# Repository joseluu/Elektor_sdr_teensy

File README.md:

### SDR front end for teensy and teensy audio

This frontend board stacks on top of a teensyaudio board which iself is stacked on the teensy.

<p align="center">
  <table style="width:100%">
    <tr>
      <td></td>
      <td></td>
      <td></td>
      <td></td>
    </tr>
  </table>
</p>

Teensy 4.0 is used, schematic is heavily inspired by the Elektor board: https://www.elektormagazine.fr/labs/software-defined-radio-sdr-shield-for-arduino-150515-1

The differences are:

The frequency is not divided by 4 to make quadrature signals (no 7474 flipflops), rather the quadrature will have to be generated by the si5351.
A provision for an external oscillator input is made (V1.0 only), it uses a separate SMA

PCB layout attempts to minimize noise with separate ground planes for digital and analog

Versions (V2.0 is in its own branch):

<p align="center">
</td>
</p>

V 1.1 fixes a cabling error to two of the 6022 op-amps, removes the external oscillator input, internally connects the 3rd output of the si5351 frequency synthetiser to the input allowing fot tests and calibration of the signal path

V 1.1 uses a 74HC4066 multiplexer and is good to 30MHz, has a cabling error underneath where the zero ohm resistor connecting the 2 ground plane is not connected on one side.

V 2.0 uses a SN74CBTL3253 and should be good to 150MHz (work in progress, not tested yet)

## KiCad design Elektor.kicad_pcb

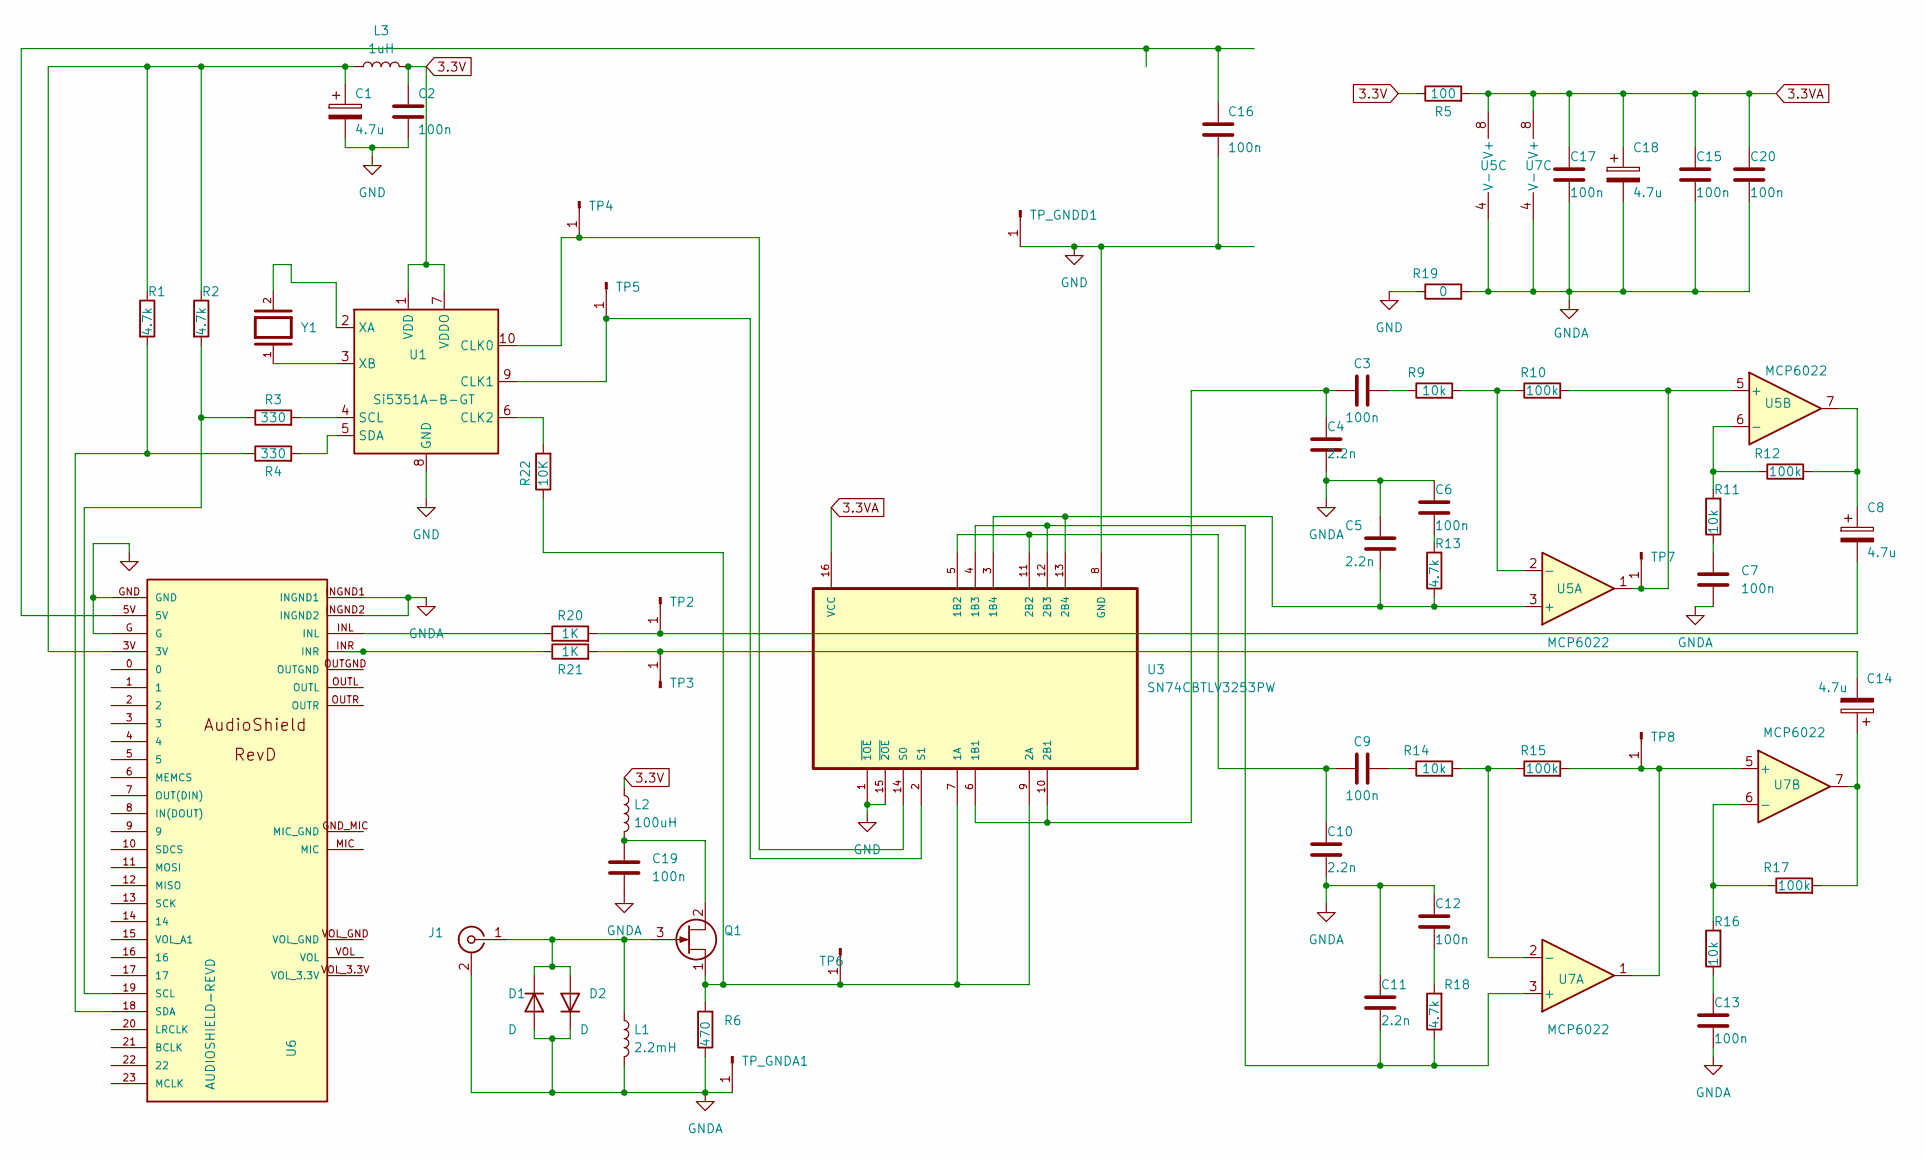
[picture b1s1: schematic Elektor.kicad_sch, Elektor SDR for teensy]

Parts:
C1, C8, C14, C18: 4.7u; C_Rect_L4.0mm_W2.5mm_P2.50mm
C2, C3, C6, C7, C9, C12, C13, C15, C16, C17, C19, C20: 100n; C_0603_1608Metric
C4, C5, C10, C11: 2.2n; C_0603_1608Metric
D1, D2: D; D_SOD-123
J1: Conn_Coaxial; SMA_Samtec_SMA-J-P-X-ST-EM1_EdgeMount
L1: 2.2mH; L_1812_4532Metric
L2: 100uH; L_1210_3225Metric
L3: 1uH; L_0805_2012Metric_Pad1.05x1.20mm_HandSolder
Q1: BF545B; SOT-23
R1, R2, R13, R18: 4.7k; R_0603_1608Metric
R3, R4: 330; R_0603_1608Metric
R5: 100; R_0603_1608Metric
R6: 470; R_0603_1608Metric
R9, R11, R14, R16: 10k; R_0603_1608Metric
R10, R12, R15, R17: 100k; R_0603_1608Metric
R19: 0; R_0603_1608Metric
R20, R21: 1K; R_0603_1608Metric
R22: 10K; R_0402_1005Metric
TP2, TP3, TP4, TP5, TP6, TP7, TP8: Conn_01x01_Pin; Test_point_jose_D1.8mm_Drill1.0mm
TP_GNDA1: Conn_01x01_Pin; Test_point_jose_D1.8mm_Drill1.0mm
TP_GNDD1: Conn_01x01_Pin; Test_point_jose_D1.8mm_Drill1.0mm
U1: Si5351A-B-GT; MSOP-10_3x3mm_P0.5mm
U3: SN74CBTLV3253PW; TSSOP-16_4.4x5mm_P0.65mm
U5, U7: MCP6022; SOP-8_3.9x4.9mm_P1.27mm
U6: AUDIOSHIELD-REVD; AUDIOSHIELD-REVD-Simplified
Y1: ABM7-25.000MHZ-D2Y-T; XTAL_ABM7-16.000MHZ-D2Y-T; PARTREV 9/3/2019

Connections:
3.3V: C2.1, L2.1, L3.2, R5.1, U1.1 (VDD), U1.7 (VDDO)
3.3VA: C15.1, C17.1, C18.1, C20.1, R5.2, U3.16 (VCC), U5.8 (V+), U7.8 (V+)
GND: C1.2, C2.2, C16.2, R19.1, TP_GNDD1.1, U1.8 (GND), U3.1 (~1OE), U3.8 (GND), U3.15 (~2OE), U6.G, U6.GND
GNDA: C4.1, C5.2, C6.1, C7.1, C10.1, C11.2, C12.1, C13.1, C15.2, C17.2, C18.2, C19.2, C20.2, D1.2 (A), D2.1 (K), J1.2 (Ext), L1.2, R6.1, R19.2, TP_GNDA1.1, U5.4 (V-), U6.INGND1, U6.INGND2, U7.4 (V-)
unnamed: C1.1, L3.1, R1.1, R2.1, U6.3V
unnamed: C3.2, R9.1
unnamed: C6.2, R13.2
unnamed: C7.2, R11.1
unnamed: C8.1, R12.2, U5.7
unnamed: C9.2, R14.1
unnamed: C12.2, R18.2
unnamed: C13.2, R16.1
unnamed: C14.1, R17.2, U7.7
unnamed: C16.1, U6.5V
unnamed: D1.1 (K), D2.2 (A), J1.1 (In), L1.1, Q1.3 (G)
unnamed: C19.1, L2.2, Q1.2 (D)
unnamed: Q1.1 (S), R6.2, R22.1, TP6.1, U3.7 (1A), U3.9 (2A)
unnamed: R20.1, U6.INL
unnamed: R21.1, U6.INR
unnamed: C8.2, R20.2, TP2.1
unnamed: C14.2, R21.2, TP3.1
unnamed: TP4.1, U1.10 (CLK0), U3.14 (S0)
unnamed: TP5.1, U1.9 (CLK1), U3.2 (S1)
unnamed: R10.2, TP7.1, U5.1, U5.5 (+)
unnamed: R15.2, TP8.1, U7.1, U7.5 (+)
unnamed: R22.2, U1.6 (CLK2)
unnamed: R3.2, U1.4 (SCL)
unnamed: R4.2, U1.5 (SDA)
unnamed: U1.2 (XA), Y1.2
unnamed: U1.3 (XB), Y1.1
unnamed: C3.1, C4.2, U3.6 (1B1), U3.10 (2B1)
unnamed: C9.1, C10.2, U3.5 (1B2), U3.11 (2B2)
unnamed: C11.1, R18.1, U3.4 (1B3), U3.12 (2B3), U7.3 (+)
unnamed: C5.1, R13.1, U3.3 (1B4), U3.13 (2B4), U5.3 (+)
unnamed: R9.2, R10.1, U5.2 (-)
unnamed: R11.2, R12.1, U5.6 (-)
unnamed: R2.2, R3.1, U6.19 (SCL)
unnamed: R1.2, R4.1, U6.18 (SDA)
unnamed: R14.2, R15.1, U7.2 (-)
unnamed: R16.2, R17.1, U7.6 (-)

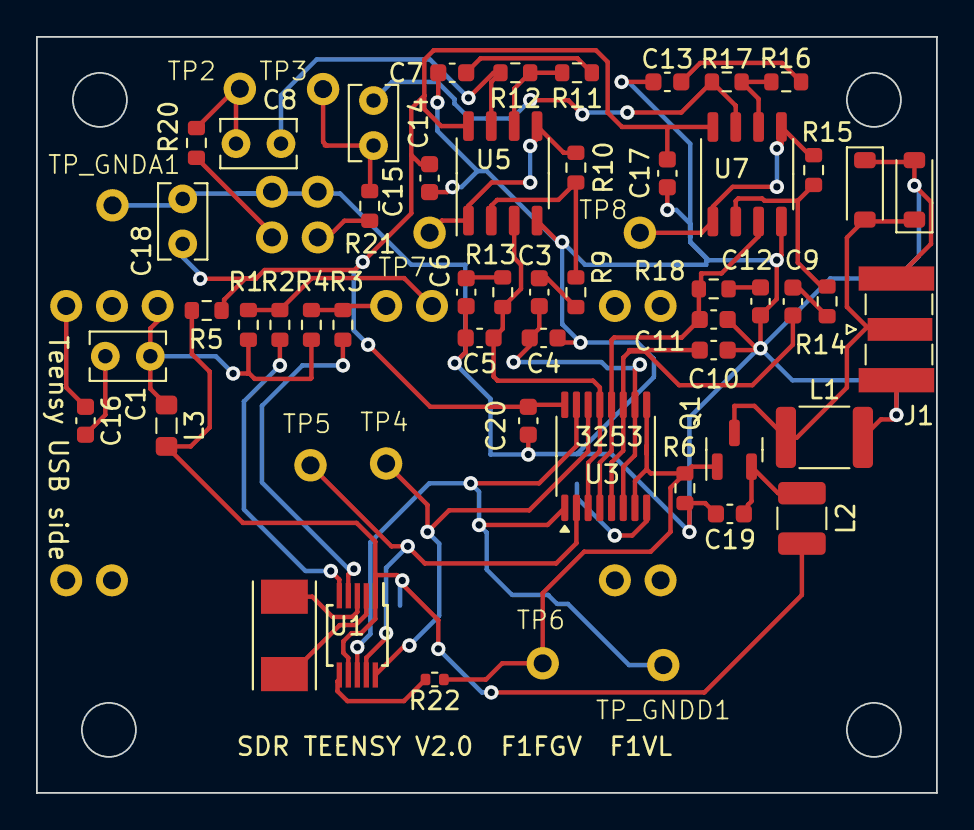
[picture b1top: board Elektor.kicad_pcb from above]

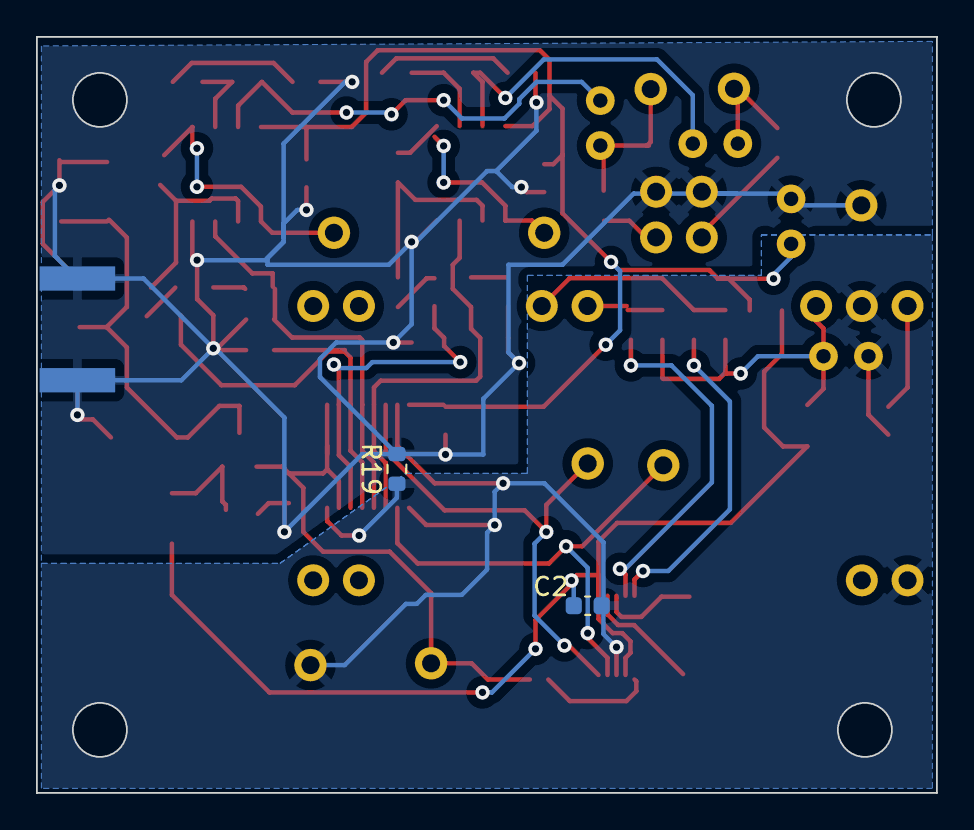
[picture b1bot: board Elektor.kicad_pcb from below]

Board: 2 copper layers, 50.0 x 42.0 mm, 62 parts (2 on the bottom side), 40 nets.

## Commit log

2024-08-16 fix .gitignore
2024-08-16 mise a jour pdf schema
2024-08-19 routage plus compact
2024-08-20 avec plan de masse
2024-08-20 meilleur plan de masse
2024-08-21 plus compact
2024-08-21 ajout connexion manquante
2024-08-21 4066 avait 16 broches au lieu de 14 !
2024-08-21 alternative layout first commit
2024-08-21 pousse U1 a droite pour plus de compacite
2024-08-22 amelioration liaison des 2 masses
2024-08-23 SMA generateur externe à gauche
2024-08-23 SMA generateur externe à gauche + pdf oublie
2024-08-24 decouplages, capa de liaison generateur externe, marges de prehension, trous de fixations
2024-08-24 marquage
2024-08-27 release to manufacturing
2025-02-23 debut V2
2025-06-13 release V1.1
2025-06-14 version 2.0 using a SN74CBTLV3253
2025-12-24 correct pdf schematic
2025-12-24 rename pdf schematic to V2
2025-12-26 Add the V1.0 schematic
2026-01-06 add pictures
2026-01-06 more details in readme
2026-01-06 make kicad langage recognized by github
